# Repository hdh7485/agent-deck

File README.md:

# Agent Deck

Codex, Hermes, OMX, tmux 같은 AI 에이전트 작업을 물리적으로 제어하고 상태를 RGB로 표시하는 데스크톱 컨트롤러 프로젝트입니다.

이 프로젝트는 공개된 제품 경험을 참고하되, 공개되지 않은 OpenAI Micro의 회로·펌웨어·프로토콜을 추정하거나 복제하지 않습니다. 목표는 기능적으로 유사한 사용자 경험을 제공하는 독자 설계입니다.

## V1 범위

- PCB 고정형 MX 호환 기계식 키 12개, Kailh 핫스왑 소켓, 키별 다이오드. 터치 오른쪽 K11은 기본 2u 마이크/PTT 키
- 전체 12키 개별 RGB 상태 표시
- 클릭 가능한 로터리 엔코더 1개
- 낮은 원형 오목 캡을 씌운 5방향 디지털 내비게이션 스위치 1개
- 단일 원형 정전식 터치 패드 1개
- XIAO ESP32-S3 Plus와 XIAO nRF52840 Plus 비교 평가
- USB HID, Vendor HID, BLE HID 및 상태 통신 실험
- Codex/Hermes/OMX/tmux 상태를 정규화하는 PC 브리지
- USB 전원 우선 검증 후 1셀 Li-Po 평가

OLED나 LCD는 사용하지 않습니다. 모든 입력 부품은 브레드보드가 아니라 입력 PCB에 직접 실장합니다.

## 현재 기준 설계

V1은 공용 입력 PCB와 MCU별 어댑터 보드를 사용합니다. 입력 PCB에는 키 매트릭스, MCP23017, 내비게이션 스위치, 정전식 터치 IC, 엔코더, RGB LED 및 전원 보호 회로를 두고, 어댑터는 XIAO 보드별 핀·전원·USB 차이를 흡수합니다.

- 키 12개: 5핀 MX 호환 스위치, Kailh `CPG151101S11-16` 핫스왑 소켓, 다이오드를 포함한 4×4 매트릭스. K11은 호스트 음성 입력을 누르는 동안만 여는 기본 PTT 매핑
- MCP23017: 키 매트릭스, 5방향 스위치, 터치 출력 처리
- 엔코더 A/B/클릭: MCU 직접 연결
- 터치: AT42QT1010 계열 외부 IC 우선
- RGB: 5V 주소 지정 LED, 74AHCT1G125 레벨 시프터, 전류 제한 전원 스위치
- USB-C: V1에서는 장착한 XIAO의 온보드 USB-C를 케이스 밖으로 노출
- 배터리: 어댑터 측에서 각 XIAO의 충전·배터리 회로를 사용하고 공용 PCB에 충전기를 중복하지 않음

정확한 주문 부품과 보드 리비전은 [V1 핏체크 부품 기준](docs/hardware/v1-fit-check-parts.md)에 따라 실물 샘플과 공식 도면으로 다시 잠급니다.

## KiCad V1 엔지니어링 드래프트

현재 저장소에는 다음 실제 KiCad 설계 소스가 있습니다.

- 공용 입력 PCB: 12키, 12다이오드, 키별 RGB 12개, MCP23017, EC11, 5방향 입력, AT42QT1010 터치, TPS2553 RGB 전류 제한, AHCT 레벨 시프터
- XIAO ESP32-S3 Plus 전용 어댑터
- XIAO nRF52840 Plus 전용 어댑터
- 세 보드의 블록 회로도와 재현 가능한 생성 스크립트

이 파일은 부품 배치, 전기 넷, 기구 기준점을 검토하기 위한 엔지니어링 드래프트입니다. 세 블록 회로도는 ERC 0건이며 현재 배치에서 DRC 오류도 0건이지만, 공용 PCB 117개와 각 어댑터 21개의 연결이 의도적으로 미배선 상태입니다. 블록 회로도는 아직 PCB 전체 부품과 1:1 패리티를 갖는 제작 회로도가 아닙니다. 따라서 현재 파일은 PCB 제작용 릴리스가 아닙니다. 검증 결과와 제작 중지 조건은 [KiCad 검증 기록](hardware/kicad/VALIDATION.md)에 있습니다.

## 3D 프린트 케이스 핏체크

현재 PCB 좌표에서 생성한 하판, 상부 베젤, 12키 1.5 mm MX 플레이트 STL이 `mechanical/exports/v1-fit-check/`에 있습니다. 공개 외형처럼 상단은 엔코더–키 2개–내비게이션 컨트롤, 하단은 터치–2u PTT–보조 키로 배치했습니다. 모든 키캡은 각인 없는 검정 반투명 스모크 재질을 의도하며, 1u와 2u 키를 19 mm 격자와 1.8 mm 명목 간격으로 정렬했습니다.

공용 PCB는 100 × 100 mm, 케이스 몸체는 107.8 × 107.8 × 33.17 mm입니다. 내부 모델은 81 × 43 mm MCU 어댑터, 7.47 mm 커넥터 핏체크 스택, XIAO/USB 및 RF 영역, 34.5 × 45 × 6 mm 배터리 후보, U1·C30·핫스왑 소켓, 2u 스태빌라이저와 케이블 여유 공간을 포함합니다. STL 세 개는 생성 시 manifold 검사를 통과했지만, 실제 부품 공차와 배터리 팽창은 샘플 조립으로 확인해야 합니다.

## 문서 지도

- [제품·물리 인터페이스 디자인 계약](DESIGN.md)
- [제품 요구사항](.omx/plans/prd-agent-deck-v1.md)
- [검증 계획](.omx/plans/test-spec-agent-deck-v1.md)
- [시스템 아키텍처](docs/architecture/system-architecture.md)
- [XIAO 핀 호환성](docs/hardware/pin-compatibility.md)
- [전기 설계 제안](docs/hardware/electrical-proposal.md)
- [부품·기구 결정 체크리스트](docs/hardware/design-inputs-checklist.md)
- [V1 핏체크 부품 기준](docs/hardware/v1-fit-check-parts.md)
- [V1 프로토타입 BOM](docs/hardware/prototype-bom.csv)
- [장치 프로토콜](docs/protocol/device-protocol.md)
- [공식 자료 목록](docs/research/source-register.md)
- [KiCad 구조](hardware/kicad/README.md)
- [KiCad 검증 기록](hardware/kicad/VALIDATION.md)
- [펌웨어 구조](firmware/README.md)
- [PC 브리지 구조](bridge/README.md)
- [기구 설계 구조](mechanical/README.md)
- [3D 프린트 케이스 핏체크](mechanical/enclosure/README.md)
- [2026-07-16 호스트·CAD 검증 증거](docs/test-evidence/2026-07-16-v1-baseline.md)

## 제작 순서

1. 두 MCU의 최소 펌웨어와 통신 경로를 개발 보드에서 검증
2. 공식 핀맵·회로도와 선택 부품 데이터시트로 회로도 작성
3. 입력 PCB와 MCU 어댑터 PCB 설계 및 DRC/ERC
4. 스위치 플레이트 설계
5. 케이스와 USB/안테나/배터리 간섭 검증
6. 조립 및 전기적 안전 검사
7. USB/BLE/입력/RGB/전력/재연결/위험 동작 E2E 테스트

## 상태

요청한 후속 작업 1~5의 저장소 기준 베이스라인을 구현했습니다.

1. 부품 후보와 주문 전 실물 확인 게이트를 문서화했습니다.
2. 배터리–MCU 어댑터–공용 PCB–플레이트 전체 케이스 스택과 출력용 STL을 만들었습니다.
3. 공용 PCB와 두 어댑터를 실제 핏체크 배치로 갱신하고 ERC/DRC를 실행했습니다.
4. ESP32-S3/nRF52840 공통 펌웨어 코어와 보드별 fail-closed 포트 골격을 구현했습니다.
5. 프로토콜, 세션 상태, 안전 정책, PTT 수명주기, fixture/tmux/Codex 읽기 전용 어댑터를 포함한 PC 브리지를 구현했습니다.

호스트 테스트와 CAD 검증은 통과했지만 실물 MCU·USB/BLE·전원·터치·RF 검증과 PCB 배선은 남아 있습니다. 특히 DRC 오류 0건은 미배선이 없다는 뜻이 아닙니다. 현재 보드는 Gerber 생성이나 주문 단계가 아닙니다.

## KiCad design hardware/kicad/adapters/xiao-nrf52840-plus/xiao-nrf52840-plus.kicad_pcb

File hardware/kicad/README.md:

# KiCad project structure

Create separate KiCad projects so common-input changes and board-specific adapter changes remain reviewable.

```text
hardware/kicad/
  input-main/
    input-main.kicad_pro
    input-main.kicad_sch
    input-main.kicad_pcb
  adapters/
    xiao-esp32s3-plus/
      xiao-esp32s3-plus.kicad_pro
      xiao-esp32s3-plus.kicad_sch
      xiao-esp32s3-plus.kicad_pcb
    xiao-nrf52840-plus/
      xiao-nrf52840-plus.kicad_pro
      xiao-nrf52840-plus.kicad_sch
      xiao-nrf52840-plus.kicad_pcb
  libraries/
    agent-deck.kicad_sym
    agent-deck.pretty/
    3dmodels/
  templates/
  scripts/
```

## Main schematic hierarchy

- `00_interface`: semantic adapter connector, test points, board identity.
- `10_keys`: 12 switches, diodes, 4×4 matrix.
- `20_io_expander`: MCP23017, address/reset, I2C, interrupts.
- `30_controls`: encoder, navigation, touch controller/electrode.
- `40_rgb`: LEDs, buffer, data resistor, decoupling.
- `50_power`: RGB load switch/current limit, rail test points, optional battery-RGB experiment kept isolated.

## Adapter schematic hierarchy

- XIAO symbol/footprint from the matching official Seeed design resources.
- Semantic connector mapping.
- USB-C access and enclosure reference.
- Battery connector/board charger interface.
- Reset/boot/debug/SWD test pads.
- Antenna keep-out and mechanical outline.
- Adapter identity.

## Library policy

- Copy only project-used symbols/footprints into the project library when licensing permits, preserving attribution and source revision.
- Verify every pad number and courtyard against the selected component drawing.
- Do not trust community footprints for XIAO bottom pads, hot-swap sockets, encoders, or navigation switches without a dimension check.
- Keep generated fabrication outputs out of Git unless a release process explicitly snapshots them.

## Coordinate contract

The common PCB origin, key centers, plate origin, mounting holes, adapter connector, USB datum, encoder axis, navigation axis, and touch center form a versioned mechanical interface. Mechanical CAD imports these coordinates; it must not re-create them by eye.

The active V1 fit-check datum is a 100 mm × 100 mm common PCB with a 90 mm square mounting-hole pattern. The plate and enclosure dimensions derived from it are recorded in `DESIGN.md`, ADR-0012, and `mechanical/exports/v1-fit-check/dimensions.json`.

## Gates

No board is ordered until exact components pass `docs/hardware/design-inputs-checklist.md`, ERC/DRC pass, official XIAO mappings are rechecked, 3D interference is reviewed, and first-article power tests are prepared.

## Generated V1 draft

The repository now contains all three KiCad projects described above. The main PCB has complete component placement and electrical net assignments. The adapter footprint and enclosure use the Samtec `HLE-110-02-G-DV-A` / `TSM-110-04-L-DV-A` pair as a 7.47 mm fit-check target, not as an order-locked promise. The adapter outline is 81 mm × 43 mm and exposes each XIAO's onboard USB-C at the right-side enclosure opening.

Long routes remain as explicit ratsnest. This is deliberate: a deterministic autorouting experiment produced real escape and via conflicts, so it was removed instead of hiding the findings with exclusions. The current DRC result is zero errors only because the retained geometry itself has no error-level collision; it does not mean the 117 common-board and 21-per-adapter open connections are complete.

Regenerate with KiCad 10.0.4's bundled Python:

```sh
/opt/homebrew/Caskroom/kicad/10.0.4/KiCad/KiCad.app/Contents/Frameworks/Python.framework/Versions/3.9/bin/python3 \
  hardware/kicad/scripts/generate_design.py
```

The generator transcribes the XIAO Plus physical land pattern from Seeed's official Plus baseboard resource and uses the conservative semantic mapping in `docs/hardware/pin-compatibility.md`. It does not claim that the two MCU boards are electrically interchangeable.

See `VALIDATION.md` for the fresh ERC/DRC evidence and the explicit fabrication stop condition.

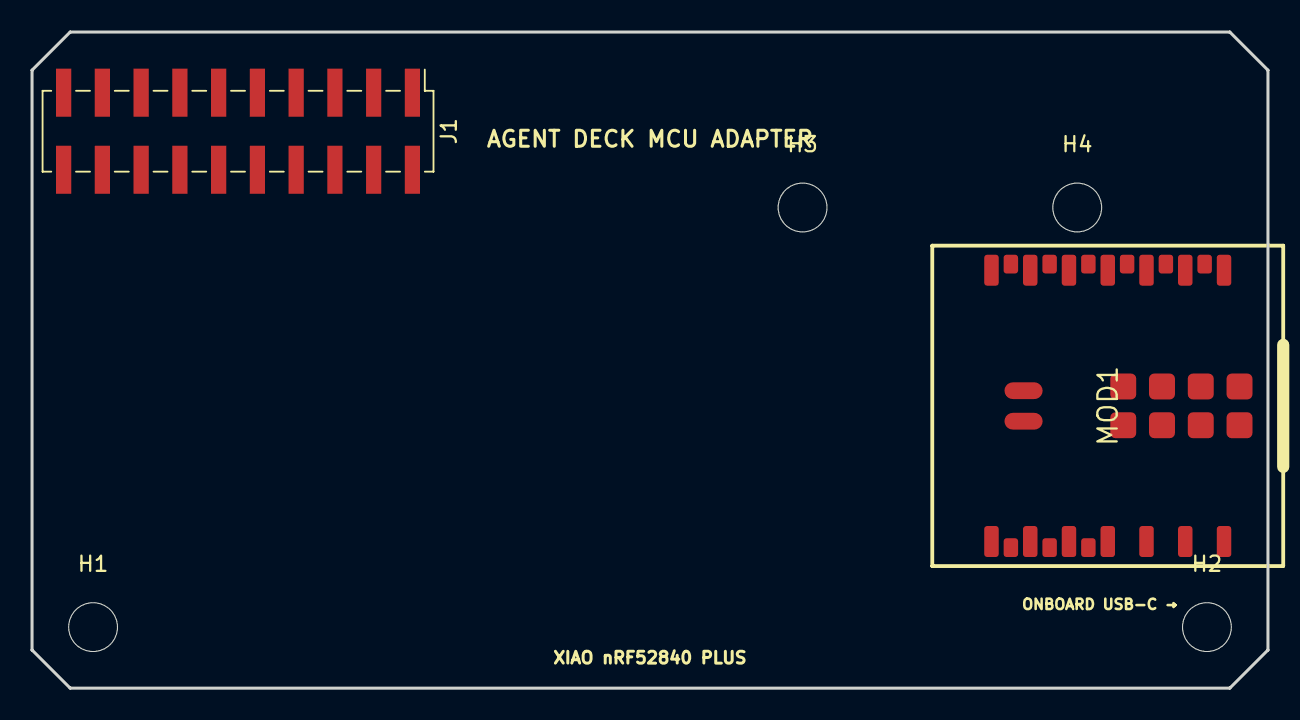
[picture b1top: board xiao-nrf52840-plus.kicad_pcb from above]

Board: 2 copper layers, 81.0 x 43.0 mm, 7 parts (1 on the bottom side), 14 nets, no tracks yet.

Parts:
H1, H2, H3, H4: M3; MountingHole_3.2mm_M3
J1: COMMON_MCU_ADAPTER_2x10 / Samtec TSM-110-04-L-DV 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; PinHeader_2x10_P2.54mm_Vertical_SMD
MOD1: XIAO nRF52840 PLUS; XIAO_Plus_Official_Base_Pattern
TP1: D16 reserved; TestPoint_Pad_D1.5mm

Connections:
+3V3: J1.1, MOD1.12
BAT_SENSE_D16_RESERVED: MOD1.20, TP1.1
ENC_A: J1.10, MOD1.9
ENC_B: J1.11, MOD1.10
ENC_SW: J1.12, MOD1.11
GND: J1.2, J1.4, J1.17, J1.18, J1.19, J1.20, MOD1.13, MOD1.27, MOD1.33
I2C_SCL: J1.6, MOD1.6
I2C_SDA: J1.5, MOD1.5
IOX_INT: J1.7, MOD1.2
RGB_DATA: J1.8, MOD1.1
RGB_PWR_EN: J1.9, MOD1.4
UART_RX_DBG: J1.14, MOD1.8
UART_TX_DBG: J1.13, MOD1.7
VBUS_5V: J1.3, MOD1.14

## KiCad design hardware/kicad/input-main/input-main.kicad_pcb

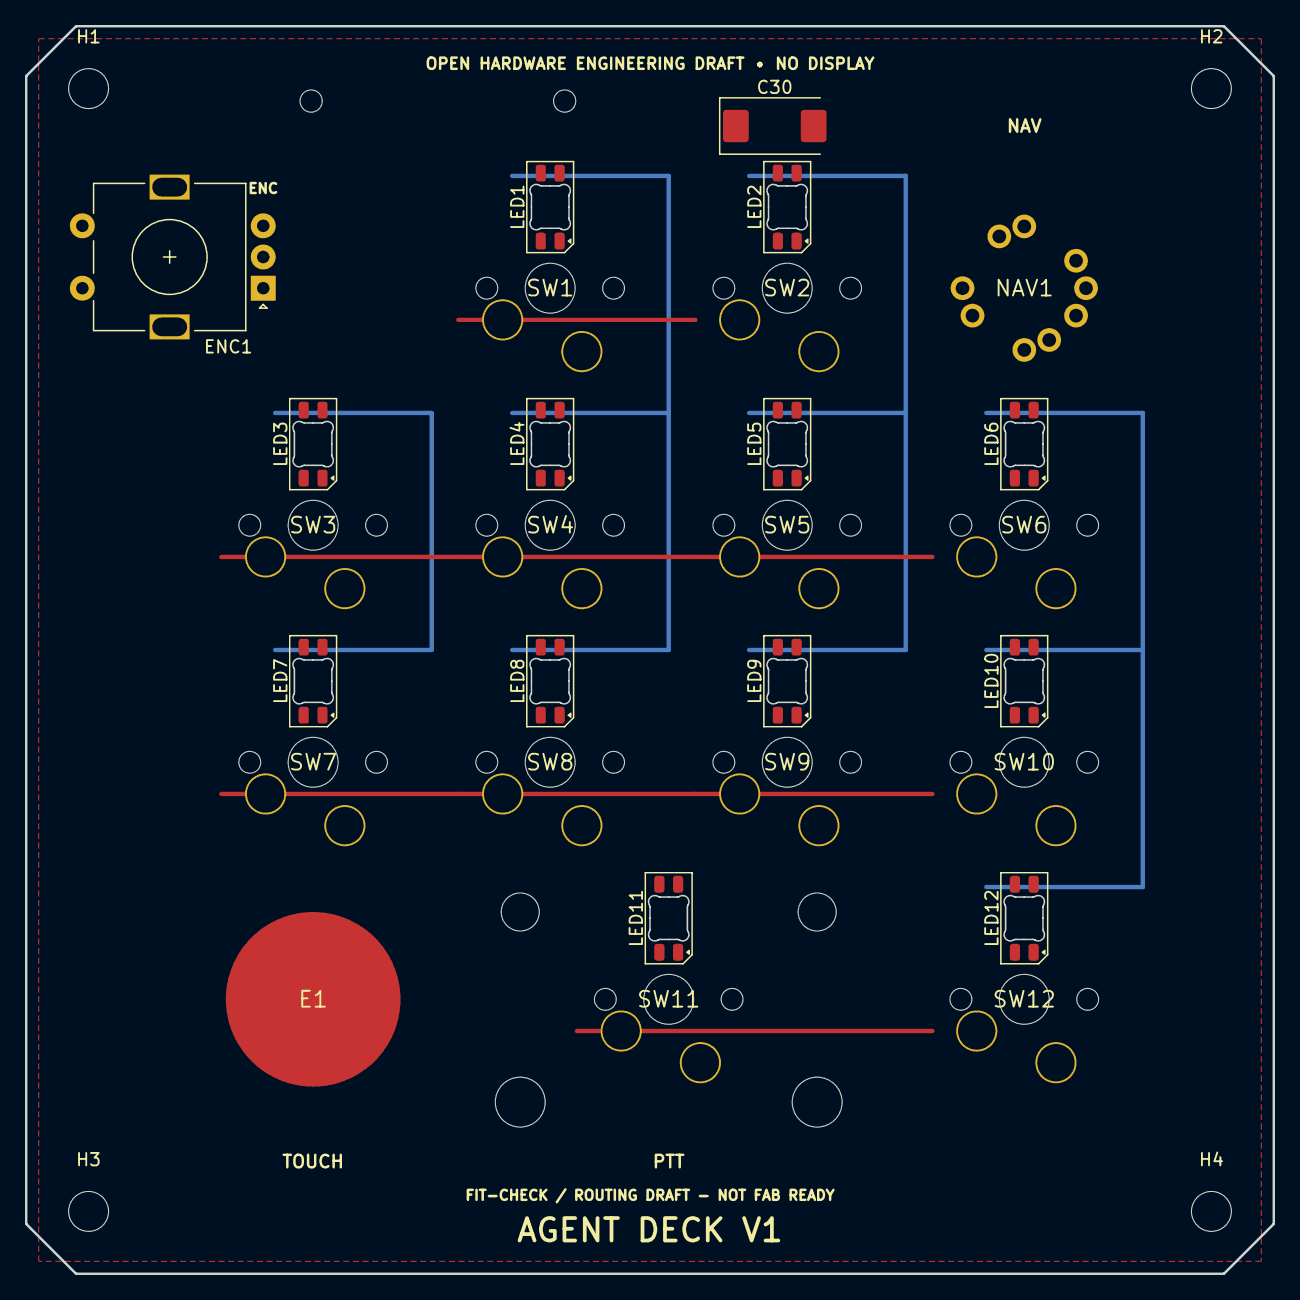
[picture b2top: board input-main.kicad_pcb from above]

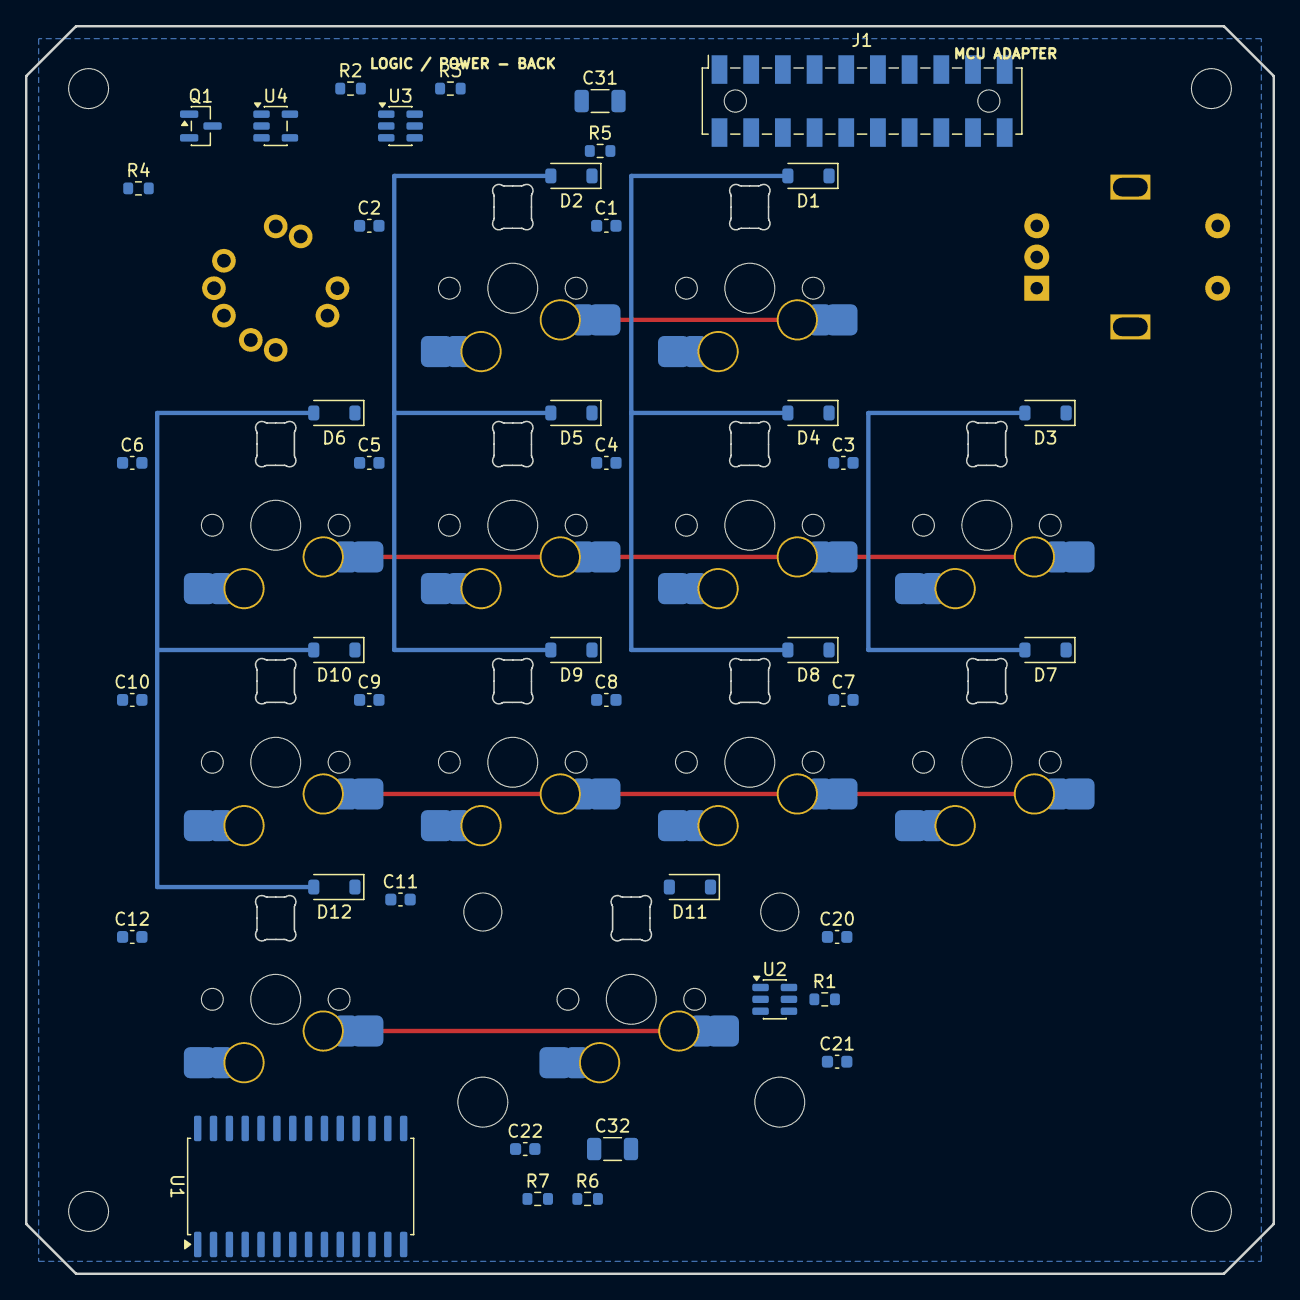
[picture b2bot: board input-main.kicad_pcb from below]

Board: 2 copper layers, 100.0 x 100.0 mm, 74 parts (42 on the bottom side), 58 nets.

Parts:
C1, C2, C3, C4, C5, C6, C7, C8, C9, C10, C11, C12: 100nF LED local; C_0603_1608Metric
C20: 10nF C0G touch candidate; C_0603_1608Metric
C21: 100nF; C_0603_1608Metric
C22: 100nF MCP23017; C_0603_1608Metric
C30: 150uF 10V low-profile polymer candidate; CP_EIA-7343-31_Kemet-D
C31: 10uF 10V X7R LED rail; C_1206_3216Metric
C32: 10uF 10V X7R 3V3 rail; C_1206_3216Metric
D1, D2, D3, D4, D5, D6, D7, D8, D9, D10, D11, D12: 1N4148W; D_SOD-123
E1: 14 mm circular touch electrode; Touch_Electrode_14mm
ENC1: EC11E15244G1 candidate; RotaryEncoder_Alps_EC11E-Switch_Vertical_H20mm
H1, H2, H3, H4: M3; MountingHole_3.2mm_M3
J1: COMMON_MCU_ADAPTER_2x10 / Samtec HLE-110-02-G-DV-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; Samtec_HLE-110-02-xxx-DV-A_2x10_P2.54mm_Horizontal
LED1, LED2, LED3, LED4, LED5, LED6, LED7, LED8, LED9, LED10, LED11, LED12: SK6812MINI-E; LED_SK6812MINI-E_3.2x2.8mm_P1.5mm_ReverseMount
NAV1: RKJXM1015004 catalog-outline fit-check / formal s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; Nav_RKJXM1015004_Catalog_Fitcheck
Q1: MMBT3904 RGB OE inverter; SOT-23
R1: 1k touch series; R_0603_1608Metric
R2: 232k 1% ILIM (~117mA typ); R_0603_1608Metric
R3: 100k EN pulldown; R_0603_1608Metric
R4: 10k OE pullup; R_0603_1608Metric
R5: 330R RGB data; R_0603_1608Metric
R6: 4.7k SDA pullup; R_0603_1608Metric
R7: 4.7k SCL pullup; R_0603_1608Metric
SW1, SW2, SW3, SW4, SW5, SW6, SW7, SW8, SW9, SW10, SW12: CHERRY MX2A-L1NB / CPG151101S11-16 hot-swap; MX_1u_Kailh_CPG151101S11-16_Hotswap
SW11: CHERRY MX2A-L1NB 2u PTT hot-swap / KS-52B200T-01 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; MX_1u_Kailh_CPG151101S11-16_Hotswap
U1: MCP23017-E/SO; SOIC-28W_7.5x17.9mm_P1.27mm
U2: AT42QT1010-TSHR; SOT-23-6
U3: TPS2553DBVR; SOT-23-6
U4: SN74AHCT1G125DBVR; SOT-23-5

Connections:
+3V3: C21.1, C22.1, C32.1, J1.1, R6.1, R7.1, U1.9, U1.18, U2.5
COL0: D3.2, D7.2, U1.25
COL1: D1.2, D4.2, D8.2, D11.2, U1.26
COL2: D2.2, D5.2, D9.2, U1.27
COL3: D6.2, D10.2, D12.2, U1.28
ENC_A: ENC1.A, J1.10
ENC_B: ENC1.B, J1.11
ENC_SW: ENC1.S1, J1.12
GND: C1.2, C2.2, C3.2, C4.2, C5.2, C6.2, C7.2, C8.2, C9.2, C10.2, C11.2, C12.2, C21.2, C22.2, C30.2, C31.2, C32.2, ENC1.C, ENC1.S2, J1.2, J1.4, J1.17, J1.18, J1.19, J1.20, LED1.3, LED2.3, LED3.3, LED4.3, LED5.3, LED6.3, LED7.3, LED8.3, LED9.3, LED10.3, LED11.3, LED12.3, NAV1.6, NAV1.7, Q1.2, R2.2, R3.2, U1.10, U1.15, U1.16, U1.17, U2.2, U2.6, U3.2, U4.3
I2C_SCL: J1.6, R7.2, U1.12
I2C_SDA: J1.5, R6.2, U1.13
IOX_INT: J1.7, U1.19
K1_D: D1.1, SW1.2
K2_D: D2.1, SW2.2
K3_D: D3.1, SW3.2
K4_D: D4.1, SW4.2
K5_D: D5.1, SW5.2
K6_D: D6.1, SW6.2
K7_D: D7.1, SW7.2
K8_D: D8.1, SW8.2
K9_D: D9.1, SW9.2
K10_D: D10.1, SW10.2
K11_D: D11.1, SW11.2
K12_D: D12.1, SW12.2
LED_5V: C1.1, C2.1, C3.1, C4.1, C5.1, C6.1, C7.1, C8.1, C9.1, C10.1, C11.1, C12.1, C30.1, C31.1, LED1.1, LED2.1, LED3.1, LED4.1, LED5.1, LED6.1, LED7.1, LED8.1, LED9.1, LED10.1, LED11.1, LED12.1, U3.6
NAV_CENTER_N: NAV1.5, U1.5
NAV_DOWN_N: NAV1.2, U1.2
NAV_LEFT_N: NAV1.3, U1.3
NAV_RIGHT_N: NAV1.4, U1.4
NAV_UP_N: NAV1.1, U1.1
RGB_BUF_OUT: R5.1, U4.4
RGB_DATA: J1.8, U4.2
RGB_DIN0: LED1.4, R5.2
RGB_ILIM: R2.1, U3.5
RGB_LINK1: LED1.2, LED2.4
RGB_LINK2: LED2.2, LED3.4
RGB_LINK3: LED3.2, LED4.4
RGB_LINK4: LED4.2, LED5.4
RGB_LINK5: LED5.2, LED6.4
RGB_LINK6: LED6.2, LED7.4
RGB_LINK7: LED7.2, LED8.4
RGB_LINK8: LED8.2, LED9.4
RGB_LINK9: LED9.2, LED10.4
RGB_LINK10: LED10.2, LED11.4
RGB_LINK11: LED11.2, LED12.4
RGB_OE_N: Q1.3, R4.1, U4.1
RGB_PWR_EN: J1.9, Q1.1, R3.1, U3.3
ROW0: SW1.1, SW2.1, U1.21
ROW1: SW3.1, SW4.1, SW5.1, SW6.1, U1.22
ROW2: SW7.1, SW8.1, SW9.1, SW10.1, U1.23
ROW3: SW11.1, SW12.1, U1.24
SPARE0: J1.15, U1.7
SPARE1: J1.16, U1.8
TOUCH_ELECTRODE: E1.1, R1.1
TOUCH_OUT: U1.6, U2.1
TOUCH_SNS: C20.2, U2.4
TOUCH_SNSK: C20.1, R1.2, U2.3
VBUS_5V: J1.3, R4.2, U3.1, U4.5
